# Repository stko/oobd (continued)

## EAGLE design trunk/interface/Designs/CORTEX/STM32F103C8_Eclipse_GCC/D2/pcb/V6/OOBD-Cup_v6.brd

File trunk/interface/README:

The interface structure

OOBD might have many different hardware realisations (Designs), but always a common software core. To handle them all in one repository, they are seperated into different Design- Folders (Dxx). To make it simple, these designs just get a different number.

These designs contains both the hardware description files (Schematics, PCB, etc) and also the software abstraction layers, which connects the abstract functions to the real hardware and do also all the low level data handling like e.g.  the CAN -Bus

The core functions are all hardware independend and so not bounded to the design folders. They are also splitted into the protocol- specific protocol handlers (proto), the runtime system (os) and the client-interface (oobd), which handles the data exchange with the connected client.

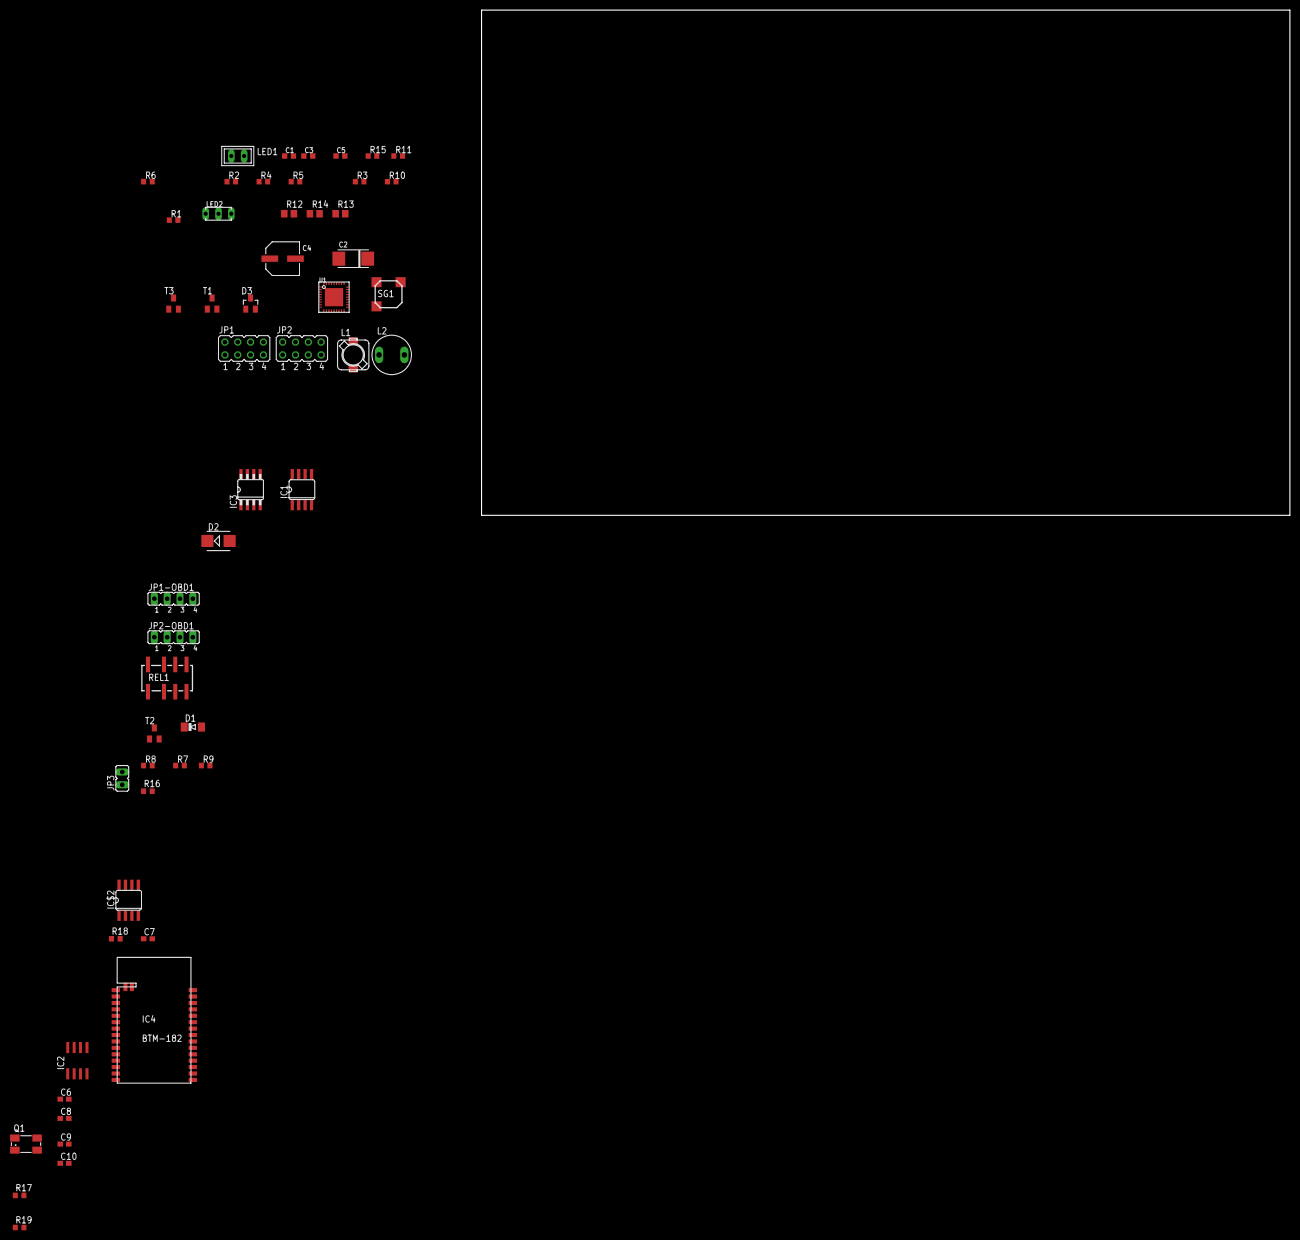
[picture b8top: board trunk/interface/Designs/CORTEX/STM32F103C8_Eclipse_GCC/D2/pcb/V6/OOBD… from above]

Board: 2 copper layers, 160.0 x 100.0 mm, 53 parts (0 on the bottom side), 40 nets, no tracks yet.

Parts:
C1: 1µF; C0603K
C2: 220µF; C6032-TE-C
C3: 220pF; C0603K
C4: 47µ/35V; SV-D
C5: 100nF; C0603K
C6, C8: 100n; C0603
C7: 10nF; C0603
C9, C10: 15p; C0603
D1: 1N4148; MINIMELF
D2: B140; SMB
D3: BAS40; SOT23
IC1: PCA82C250T; SO08
IC2: 78L05SMD; SO08
IC3: MC34063-SO; SO8
IC4: BTM-182
IC$2: SI9243AEY; SO08
JP1: Program; JP4Q
JP1-OBD1, JP2-OBD1: JP4
JP2: SPI / SD-Card; JP4Q
JP3: JP1
L1: 47uH; PIS2408
L2: 47µH; 07HCP-XXXX-50
LED1: Blue; U57X32
LED2: Rt/Gr; DUOLED2X5
Q1: 8MHz; CTS406
R1, R3: 82R; R0603
R2, R4, R7, R10: 4k7; R0603
R5, R6, R17, R19: 10k; R0603
R8: 180k; R0603
R9: 47k; R0603
R11: 3k3; R0603
R12, R13, R14: 1R; R0805
R15: 5k6; R0603
R16: 120R; R0603
R18: 510R; R0603
REL1: FTR-B4GA
SG1: MBWOE; BME0603SA
T1, T2, T3: BC817; SOT23
U1: STM32F10XTXU6; VFQFPN36

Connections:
+3V3: C1.1, C2.+, IC4.P$14, IC4.P$16, JP1.1, L1.P$1, L2.1, R15.2, R17.2, SG1.(+)LEAD, U1.1, U1.6, U1.19, U1.27
+5V: C8.1, IC1.3, IC2.1, IC$2.3
+12V: C4.+, C5.1, C6.1, D1.C, D2.C, IC2.8, IC3.6, LED1.A, R12.2, R13.2, R14.2, REL1.1
A0: JP2.3, R10.1
BOOT0: JP1.2, R19.2, U1.35
BTM_RX: IC4.P$10, JP1.8
BTM_TX: IC4.P$9, JP1.6
GND: C1.2, C2.-, C3.2, C4.-, C5.2, C6.2, C7.2, C8.2, C9.1, C10.1, D3.1, IC1.2, IC1.8, IC2.2, IC2.3, IC2.6, IC2.7, IC3.4, IC4.P$15, IC$2.5, JP1.3, JP2-OBD1.3, LED2.K, R5.2, R6.2, R9.1, R11.2, R19.1, T1.2, T2.2, T3.2, U1.5, U1.18, U1.26, U1.36
HS_CAN-H: JP1-OBD1.1, REL1.2
HS_CAN-L: JP1-OBD1.2, REL1.7
K-LINE: C7.1, IC$2.6, JP2-OBD1.2, R18.1
L-LINE: IC$2.8, JP2-OBD1.1
MODE1: R5.1, R6.1
MS_CAN-H: JP1-OBD1.3, REL1.4
MS_CAN-L: JP1-OBD1.4, REL1.5
unnamed: C10.2, Q1.1, U1.2
unnamed: C9.2, Q1.3, U1.3
unnamed: IC1.6, JP3.1, REL1.6
unnamed: LED2.AR, R3.2
unnamed: IC1.7, R16.2, REL1.3
unnamed: LED2.AG, R1.2
unnamed: LED1.K, R4.1
unnamed: R2.2, T1.1
unnamed: R4.2, T1.3
unnamed: C3.1, IC3.3
unnamed: IC3.1, IC3.7, IC3.8, R12.1, R13.1, R14.1
unnamed: IC3.5, R11.1, R15.1
unnamed: D3.3, IC3.2, L1.P$2, L2.2
unnamed: JP3.2, R16.1
unnamed: R7.2, T2.1
unnamed: SG1.(-)LEAD, T3.3
unnamed: R10.2, T3.1
unnamed: D1.A, R8.2, REL1.8, T2.3
REL_DIAG: R8.1, R9.2
RESET-: JP1.4, R17.1, U1.4
RX_K: IC$2.1, U1.10
STM_RXD: JP1.5, U1.22
STM_TXD: JP1.7, U1.21
TX: IC$2.4, U1.9
VBAT: D2.A, IC$2.7, JP2-OBD1.4, R18.2

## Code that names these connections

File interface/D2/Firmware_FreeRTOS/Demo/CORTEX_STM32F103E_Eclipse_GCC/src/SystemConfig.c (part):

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	 * PA 8 = DXM1 IO Pin 21  = GPIO_Mode_AIN - OOBD-Cup v5 Hardware identification
	 * PA 9 = USART1_Tx       = GPIO_Mode_AF_PP - Alternate Function output Push Pull
	 * PA10 = USART1_Rx       = GPIO_Mode_AIN - Input floating for low power consumption
	 * PA11 = USART1_CTS      = GPIO_Mode_AIN - currently unused
	 * PA12 = USART1_RTS      = GPIO_Mode_AIN - currently unused
	 * PA13 = ???             = GPIO_Mode_AIN - Input floating for low power consumption
	 * PA14 = ???             = GPIO_Mode_AIN - Input floating for low power consumption
	 * PA15 = ???             = GPIO_Mode_AIN - Input floating for low power consumption
	 * --------------------------------------------------------------------------
	 */
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	/* General settings for GPIOs of PORT A */
	GPIO_InitStructure.GPIO_Speed = GPIO_Speed_50MHz;

	/* Initialize USART2 on PA2 (USART2_Tx) and PA3 (USART2_Rx) for K-Line interface */
	GPIO_InitStructure.GPIO_Mode = GPIO_Mode_AF_PP;
	GPIO_InitStructure.GPIO_Pin = GPIO_Pin_2;
	GPIO_Init(GPIOA, &GPIO_InitStructure);
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	 * PB 1 = ??? = GPIO_Mode_AIN - Input floating for low power consumption
	 * PB 2 = ??? = GPIO_Mode_AIN - Input floating for low power consumption
	 * PB 3 = ??? = GPIO_Mode_AIN - Input floating for low power consumption
	 * PB 4 = DXM1 IO Pin 13, LED2 - red = GPIO_Mode_Out_OD - Output open drain
	 * PB 5 = DXM1 IO Pin 12, LED1 - green = GPIO_Mode_Out_OD - Output open drain
	 * PB 6 = 24LC16, SCL = GPIO_Mode_AF_OD = Alternate Function output open drain
	 * PB 7 = 24LC16, SDA = GPIO_Mode_AF_OD = Alternate Function output open drain
	 * --------------------------------------------------------------------------
	 * PB 8 = TJA1050 Pin 4 (RxD)  = GPIO_Mode_IPU - Input Pullup
	 * PB 9 = TJA1050 Pin 1 (TxD)  = GPIO_Mode_AF_PP - Alternate Function output Push Pull
	 * PB10 = DXM1 IO Pin 15, LCD out  = GPIO_Mode_AIN - currently unused
	 * PB11 = DXM1 IO Pin 18, A0 out   = OOBD-Cup v5 PWM out for buzzer
	 * PB12 = DXM1 IO Pin 19, SPI_CS   = GPIO_Mode_AIN - currently unused
	 * PB13 = DXM1 IO Pin 20, SPI_SCK  = GPIO_Mode_AIN - currently unused
	 * PB14 = DXM1 IO Pin 22, SPI_MISO = GPIO_Mode_AIN - currently unused
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
	/* Identify on which hardware the firmware is running */
	if (GPIO_ReadInputDataBit(GPIOA, GPIO_Pin_8) == Bit_RESET) { /* OOBD-Cup v5 */
		/* configure DXM1-Output (push pull) of Duo-LED1 - green (PB5) and LED2 - red (PB4) */
		GPIO_PinRemapConfig(GPIO_Remap_SWJ_NoJTRST, ENABLE); /* release alternative GPIO function of PB4 */
		GPIO_InitStructure.GPIO_Pin = GPIO_Pin_4 | GPIO_Pin_5;
		GPIO_InitStructure.GPIO_Mode = GPIO_Mode_Out_PP;
		GPIO_Init(GPIOB, &GPIO_InitStructure);
	} else if (GPIO_ReadInputDataBit(GPIOA, GPIO_Pin_8) == Bit_SET) { /* Original DXM1 */
		/* configure DXM1-Output (open drain) of LED1 - green (PB5) and LED2 - red (PB4) */
		GPIO_PinRemapConfig(GPIO_Remap_SWJ_NoJTRST, ENABLE); /* release alternative GPIO function of PB4 */
		GPIO_InitStructure.GPIO_Pin = GPIO_Pin_4 | GPIO_Pin_5;
		GPIO_InitStructure.GPIO_Mode = GPIO_Mode_Out_OD;
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
	/* Identify on which hardware the firmware is running */
	if (GPIO_ReadInputDataBit(GPIOA, GPIO_Pin_8) == Bit_RESET) {
		/* configure PB11 PWM output for buzzer, TIM2 source for OOBD-Cup v5 */
		GPIO_PinRemapConfig(GPIO_PartialRemap2_TIM2, ENABLE); /* OOBD-Cup v5, map TIM2 to PB11 */
		GPIO_InitStructure.GPIO_Mode = GPIO_Mode_AF_PP; /* OOBD-Cup v5 */
		GPIO_InitStructure.GPIO_Pin = GPIO_Pin_11;
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	//  GPIO_Init(GPIOB, &GPIO_InitStructure);

	/** --------------------------------------------------------------------------
	 * PC13 = ??? = GPIO_Mode_AIN - Input floating for low power consumption
	 * PC14 = DXM1 IO Pin 29 = GPIO_Mode_AIN - currently unused
	 * PC15 = DXM1 IO Pin 28 = GPIO_Mode_Out_PP - Plush-Pull
	 * --------------------------------------------------------------------------
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
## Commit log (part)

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2015-11-29 Scriptengine is now clearly terminated when ending script, comport is closed
    Up to now a scriptengine was never ended and stayed as zombie in the program.
    Now, when going back to the main screen, the engine is terminated and also the
    comport is closed, which hopefully improves the stability on weak bluetooth
    connections.
2015-12-02 add missing jssc.jar
2015-12-05 finally removed the jna lib used by purejavacomm
2015-12-06 reading from files and URLs, communicate by JSONRPC
    adding support for reading local and remote (text) files. Input can be read as whole, per line
    or, in case of JSON data, directly converted as a lua table. Also direct data exchange per JSONRPC
    is supported.
    detail syntax on http://www.oobd.org/doku.php?id=doc:lua_make-your-own-scripts#the_io_commands
2015-12-14 android- combobox code copied into OOBDesk
2015-12-24 theme selection works via GET parameter
2015-12-26 move html libs to another folder part 2
2015-12-27 fundamental change in serial_dxm, webUI now with dynamic element generation
    a very basic initialisation sequence was located in serial_dxm, which forced to load that file
    and initialize the whole serial stuff, even if not needed at all.
    this sequence is now moved into lua_utils, so this file now always need to be included (if not already
    done at all)
    the webUI now supports dynamic elements generations, which makes it basically compatible to all
    old scripts, as long as no advanced functions as file download, remote Connect etc. is needed
2015-12-29 classloader now reads from classloader resource file, no probs file or dummy dirs needed anymore
2016-01-02 writestring now with buffer support, but HTTP File upload not working at all?!?
    The scipt writestring commands now supports the modifier commands and get proberly
    handled in the browser (although some more user convinence need to be added),
    but the try to add NanoHTTP file upload capabilities ended up in a dependency & compile desaster,
    so "read file" support (through the browser) is not solved yet anyhow....
2016-01-04 multiScript Archives start to function
2016-01-06 add missing files
2016-01-16 lost SSL certificate re-implementend and cleaned up
2016-01-18 webUI can now start script with connection type acc. to settings
2016-01-23 adding comboboxes etc. into generic webUI script page
2016-01-24 webUI now with pgp passprase input field to use also pgp scripts
2016-01-31 webUI now with a kind of build-in filesystem to download several writestring buffers
2016-02-07 Posix Firmware now with command line parameters for more flexible testing configurations
2016-02-13 kadaver endpoint written in python for testing
2016-02-20 Function-freeze Level reached
    This is the first, reference version of the final function content of OOBD. As of todays
    knowledge, this software now contains everything which has been found as necessary to have.
    After having this, we now move over to spread the functionality into the other platforms,
    do some bug hunting and clean up, but more functions should not be expected. Also the old
    GUI will removed in parallel.
    Thanks to all team members, namely Mike, Wolfgang(s), Josef, Uli, Alex (and even Ekkehard in his role as
2016-02-27 clear termination on script load error, physical Web now starts in background thread
    this commit fixes #189 (script engine can't be stopped anymore when having a lua script
    error (tried to call nil exeption) when starting script initially
    Physical Web mDNS service is now started in background thread, which avoids blank window at
    startup
2016-02-29 css in progress
2016-03-10 Initial Readme.md with info from oobd.org
    ToDo:
    -License Text
2016-03-13 fixes #192 (engine hangs on non answered user dialogs)
    this fix also clearly closes the websockets when (re-)loading pages, so the test scripts needed
    to be adjusted also
2016-03-15 introduce tester present enable/disable function
2016-03-16 ui work, what a surprise..
2016-03-25 Verzeichnis enhaelt jetzt noch die Schematics & PCB von Audiocape und die aktualisierten Dateien von OOBD-Tiger V2. Im Moment in das falsche IC TLV320AIC3104. Housing und Package vom TLV320AIC3107 mü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
2016-03-28 add startup menu data
2016-04-04 fix missing initial settings when installed with admin rights
    try to fix #204 by writing the settings by the installer into HKLM when
    running as admin and copy it later from there by the app when it doesn't find
    settings in HKCU
2016-04-10 Erstes Update mit TLV320AIC3107. Anschluss an am3352 fehlt.
2016-04-18 correct typo of math(.)floor
2016-04-21 copied lua libraries from webUI branch
2016-04-23 try to fix wrong copy operation
2016-04-24 still helpless tryouts on proguard regarding #210
2016-05-01 "Lost connection" added
    Up to now it was quite unclear if an answer from the dongle was empty as such or if there is no
    connection to the dongle anymore it all.
    Now the function echoWrite(stringToSend) reports back, if the sented string did came back from
    the dongle as echo, or if even this feedback is missing, which indicates a broken connection
    to the dongle itself.
    As echoWrite() shall not be used in user applications, this new feature is implemented now in the
2016-05-03 just moving files
2016-05-08 transfering webUI into Android - 1000$ reward for everybody who can compile it as is :-)
2016-05-22 Live from IC Bremen-Cologne: fix #215: Firmware raw can zero delay bug
2016-05-26 Modifications on OOBD-Tiger schematics: - separate physical blocks (CAN, USB, Connectors, Ausio, Power Supply) to different pages - delete unneeded parts (so far) - replace OBD2-Interface connector t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
2016-06-04 removed hard coded web socket port assignment
2016-06-05 updated proguard to java 8.0, info graphic added
2016-06-07 Naming of Blen and BPos for packaged Data was wrong, should be bitLen and bitPos fixes #221
2016-06-10 modify USB-OTG and USB-Host interface
2016-06-14 - fix ERC (Pwr supply) issues due to faulty GL850G symbol - exchange ISO1050 against ADMU3053 and limit to a max of 2x galvanic isolated CAN-Interface due to size of PCB
2016-06-16 first roughly placing of ADM3053
2016-06-19 Erster adm3053 Plazierungsversuch, Kondensatoren nahe an IC, aber nicht so nah wie in der Alpnote.
2016-06-28 add latest modifications to OOBD schematics
2016-07-03 Platzierung abgeschlossen, Anschluss LED3 und Bauteilwert L2 offen
2016-07-11 Android now again with working server cert for Kadaver
2016-07-15 bluetooth socket reconnect failure fixed
2016-07-17 fixed wrong path handling when try to import key files
2016-07-22 correct setting handling for the different connection types
2016-07-26 add PCB-POOL Standard.dru for Eagle
2016-08-02 add missing 1V8 LDO (97,1% autorouting now)
2016-08-13 Onion get function now with optional default value as preparation for new settings
2016-08-27 Modification according 107EVM
2016-09-03 adding lock checkboxes
2016-09-08 removed the IFui interface functions, just OpenXC left back
2016-09-13 further UI cleanups, missing connection type settings added to settings
2016-09-18 furhter reductions on the system interface
2016-09-27 oobdd now also works (a little bit wobbly) as system service
2016-10-09 centralized the important interface functions into the OOBD class for simplification
2016-11-01 changed CanChannel parameter to multiple channels
2016-11-13 add libsocketcan calls to change can bus, speed, and bus mode
2016-11-20 Lovely: The Can filters now also seem to work :-)
2016-11-24 no complete can interface shutdown anymore at parameter change
2016-12-04 move canlauncher over to raspi for further testing
2016-12-10 remove erroneous memory allocation call again, which causes Linux firmware randomly to crash
    Unfortunately I used a FreeRTOS malloc() in AsyncIO without including the necessary header file,
    which made the compiler to use an implizid function call, which then corrupted the Heapspace
    management, which then randomly created a segmentation fault sometimes later, when some other
    memory got allocated.
    That gave me one week of headbanging....
    While debugging this, I corrected also some harmless uninitialized variable warning messages
2016-12-26 after long search new heap support routine for no more TaskResume at VPortMalloc to avoid hang up..?
2016-12-27 finally TCP Telnet starts to work..
2017-01-30 exchange power supply circuit to MC34063
2017-02-26 add gcc directive -std=gnu11 to cover different inline declaration handling between normal and ARM gcc
2017-03-05 Robotframework now tests with Hardware-in-the-loop
    It just took a few years, but now RF runs with the following setup:
    - RF runs on a Linux maschine and talks straight via telnet to
    - the Posix firmware, running on a Raspi, which
    - is connected via mcp2515 device to a physical can bus.
    - On the bus there's also a canable device, but tuned with Mikes
    special firmware
2017-03-19 New Ping command in uds to see, who is on the bus
    New special command for the uds protocol, which allows to collect all first incoming frames
    answered from all modules on the bus when sending a tester request on a broadcast address
    All details on http://www.oobd.org/doku.php?id=doc:rfc_canuds-mode
2017-04-30 added quiet() mode to webUIclient to also use it for runscript
2017-05-20 save ongoing work
2017-05-21 mDNSDiscovery config bug fixed, which caused jmDNS to broadcast IP6 address in IP4 network
2017-06-05 error fixed, probably it was a read-only /proc in fstab, which crashes during boot
2017-07-06 working on missing parameters in quickscript
2017-07-09 Steering column test data added
2017-07-12 Install notes added
2017-07-14 Wrap up OOBD Pi Zero
2017-08-19 first working sample of new defined generic EcuFlash file format for binary flash files
2017-09-20 correct last faulty stashed commit
2017-10-03 add LM1117 library for LDO 3V3
2017-11-11 - lock position for OOBD2 connector - place all parts on PCB but minor placing optimization necessary as preparation for autorouter
2017-11-25 7 Lines left over, error checking in regards of overlap, distance and restriction done. Mike, please check the restrictions in regards of e.g mounting holes of the pizero pcb
2017-12-13 add minor modifications after schematics review
2018-01-13 - add design rules check files of different PCB manufacturer - DRC is OK (0 errors) for OOBDpiZero.dru and OSHPark-4layer.dru) - modifications on pizero dimension Library added
2018-01-17 1) correct last unrouted wire again 2) start changing GND wires to 12mil
2018-01-24 commit before creating GND plane
2018-01-27 add PDF previews/documentations of schematics/pcb
2019-03-07 adapt to local.make template to the needs of the available sources in the repo !!!Attention: Adaptation is for a cygwin installation if using the toolchain on Linux please comment/uncomment the corre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
2019-03-23 left over from Ping Mode testing
2019-04-25 add encodeUTF8 function for codetable conversion if lua io read/write file functions are used
2021-03-27 working un Vue UI
2021-05-27 Bump browserslist from 4.16.3 to 4.16.6 in /clients/oobdpwa
    Bumps [browserslist](https://github.com/browserslist/browserslist) from 4.16.3 to 4.16.6.
    - [Release notes](https://github.com/browserslist/browserslist/releases)
    - [Changelog](https://github.com/browserslist/browserslist/blob/main/CHANGELOG.md)
    - [Commits](https://github.com/browserslist/browserslist/compare/4.16.3...4.16.6)
2021-06-17 Bump postcss from 7.0.35 to 7.0.36 in /clients/oobdpwa
    Bumps [postcss](https://github.com/postcss/postcss) from 7.0.35 to 7.0.36.
    - [Release notes](https://github.com/postcss/postcss/releases)
    - [Changelog](https://github.com/postcss/postcss/blob/main/CHANGELOG.md)
    - [Commits](https://github.com/postcss/postcss/compare/7.0.35...7.0.36)
    ---
    updated-dependencies:
2022-01-15 Bump follow-redirects from 1.13.3 to 1.14.7 in /clients/oobdpwa
    Bumps [follow-redirects](https://github.com/follow-redirects/follow-redirects) from 1.13.3 to 1.14.7.
    - [Release notes](https://github.com/follow-redirects/follow-redirects/releases)
    - [Commits](https://github.com/follow-redirects/follow-redirects/compare/v1.13.3...v1.14.7)
    ---
    updated-dependencies:
    - dependency-name: follow-redirects
2022-03-29 Bump minimist from 1.2.5 to 1.2.6 in /clients/oobdpwa
    Bumps [minimist](https://github.com/substack/minimist) from 1.2.5 to 1.2.6.
    - [Release notes](https://github.com/substack/minimist/releases)
    - [Commits](https://github.com/substack/minimist/compare/1.2.5...1.2.6)
    ---
    updated-dependencies:
    - dependency-name: minimist
2022-06-23 Bump shell-quote from 1.7.2 to 1.7.3 in /clients/oobdpwa
    Bumps [shell-quote](https://github.com/substack/node-shell-quote) from 1.7.2 to 1.7.3.
    - [Release notes](https://github.com/substack/node-shell-quote/releases)
    - [Changelog](https://github.com/substack/node-shell-quote/blob/master/CHANGELOG.md)
    - [Commits](https://github.com/substack/node-shell-quote/compare/v1.7.2...1.7.3)
    ---
    updated-dependencies:
2022-12-07 Bump decode-uri-component from 0.2.0 to 0.2.2 in /clients/oobdpwa
    Bumps [decode-uri-component](https://github.com/SamVerschueren/decode-uri-component) from 0.2.0 to 0.2.2.
    - [Release notes](https://github.com/SamVerschueren/decode-uri-component/releases)
    - [Commits](https://github.com/SamVerschueren/decode-uri-component/compare/v0.2.0...v0.2.2)
    ---
    updated-dependencies:
    - dependency-name: decode-uri-component
